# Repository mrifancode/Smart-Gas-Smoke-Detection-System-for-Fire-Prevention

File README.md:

## Didukung Oleh :
>- Dosen Pengampu : Akhmad Hendriawan ST., MT. (NIP.197501272002121003)
>- Mata kuliah : Mikrokontroller
>- Program Studi : D4 Teknik Elektronika
>- Politeknik Elektronika Negeri Surabaya<br>

## 🌊Board Member :

|      NRP      |       Nama      |    Jobdesk    |   Akun |
| :-----------:|:----------------:| :------------:| :-----:|
| 2122600031    | Annisa Nurfika Rani  | UI/UX       | [Annisaranii](https://github.com/Annisaranii)
| 2122600034    | Muhammad Rif'an        |  Project Manager | [mrifancode](https://github.com/mrifancode)
| 2122600035    | Admaeny Kusumas       |    UI/UX      | [admaeny](https://github.com/admaeny)
| 2122600044    | Kurniawan Putra Sugiharto  | Hardware | [Kurniawanputraa](https://github.com/Kurniawanputraa)
| 2122600058    | Muchammad Miftahus Shouni  | Program     | [Shoniiii](https://github.com/Shoniiii)

## 🧯 Smart Gas Smoke Detection System For Fire Prevention 👨‍🚒
Proyek ini merupakan sistem deteksi dini kebakaran berbasis mikrokontroler ATmega2560 (Arduino Mega) yang mampu mengenali keberadaan gas LPG dan asap di lingkungan sekitarnya. Sistem ini dirancang untuk memberikan peringatan secara otomatis melalui alarm buzzer dan indikator LED, serta menyediakan antarmuka GUI berbasis Python untuk pemantauan jarak dekat melalui komunikasi UART (serial).

Sensor gas dan asap seperti MQ-2 digunakan untuk mendeteksi senyawa mudah terbakar seperti LPG, asap hasil pembakaran, serta uap alkohol. Ketika konsentrasi gas atau asap melebihi ambang batas tertentu, sistem akan mengaktifkan alarm buzzer yang dikendalikan oleh sinyal PWM, sehingga mampu menghasilkan bunyi dengan intensitas berbeda tergantung level bahaya.

Selain alarm suara dan LED, sistem ini juga mengirimkan informasi status ke GUI yang menampilkan kondisi real-time, seperti konsentrasi gas, status sistem (aman atau bahaya), dan log waktu kejadian. Melalui GUI, pengguna juga dapat melakukan reset alarm, mengatur ambang batas, atau mengaktifkan simulasi kondisi bahaya untuk pengujian sistem.

## LOGO PRODUK ##

## 🔥🔥 Komponen Yang Digunakan 🔥🔥
 **1. 🤖Hardware**<br>
 
    a. Arduino ATmega 2560<br>
    b. Shield PCB<br>
    c. RTC<br>
    d. Sensor Gas MQ2<br>
    e. Sensor Asap MQ135<br>
    f. Camera <br>
    g. Buzzer <br>
    h. Indikator Lampu (led) <br>

**2. 💻Software**<br>

    a. KiCad<br>
    b. Inventor<br>
    c. Visual Studio Code (VSC)<br>
    d. Figma <br>

**3. 🪛Alat**<br>

    a. Solder<br>
    b. Timah solder<br>
    c. Kabel jumper<br>
    d. Breadboard<br>
    e. Obeng<br>
    f. PCB <br>
    g. Filamen <br>

## 🧰Rangkaian Simulasi 

## 🔮Alur Kerja

## 🚨Manfaat Project 🚨
Berikut adalah manfaat-manfaat yang didapatkan dari project kami:

1. **Pencegahan dini kebakaran** dengan mendeteksi gas/asap secara cepat, sistem dapat mencegah terjadinya kebakaran besar

2. **Meningkatkan keselamatan** penghuni rumah atau area yang dipantau.

3. **Mengurangi risiko** korban jiwa dan kerugian materi akibat kebakaran melalui sistem peringatan dini.

4. **Notifikasi real-time** memudahkan pengguna dan petugas keamanan dalam mengambil tindakan segera.

## 🔌🔌 HARDWARE 🔌🔌

**Berikut adalah jalur Wiring PCB yang kami buat menggunakan KICAD**

**Berikut adalah tampilan 3D PCB yang kami buat menggunakan KICAD**

## 🖼️🖼️ Desain 3D 🖼️🖼️ ##

**Berikut adalah 3D desain tampak luar**

**Berikut adalah 3D desain tampak dalam**

**Berikut adalah 3D desain tampak atas**

## 💻Tampilan GUI ##

## 📱Tampilan GUI WEB HP ##

## Video Promosi ##
https://youtu.be/rsLVeCHrQFU?si=O-Oxz26frcK8qSIt

## Link Canva ##
https://www.canva.com/design/DAGk-WylCwI/zFOLZ6zRMfbkMm96gKlujw/edit?utm_content=DAGk-WylCwI&utm_campaign=designshare&utm_medium=link2&utm_source=sharebutton

## Link Figma ##
https://www.figma.com/design/q9YQOLq4kY5U2ptUPi1XUb/web?fuid=1499084616784662598

## 💸💸 Rancangan Anggaran Biaya 💸💸

|      Nama Barang      |       Jumlah      |    Harga    |  
| :-----------:|:----------------:| :------------:| 
| Arduino ATmega2560    | 1  | Rp 180.000    | 
| MQ-135    |    1        |  Rp 23.500 | 
| MQ-2    |    1       |    Rp 14.300      | 
| Relay dual Channel    | 1  | Rp 20.250 | 
| PCB    | 1  | Rp 2.000     | 
| Kabel USB    | 1  | Rp5.000     | 
| Kabel Jumper    | 1pack  | Rp15.000     |   
| Kabel USB    | 1  | Rp5.000     |

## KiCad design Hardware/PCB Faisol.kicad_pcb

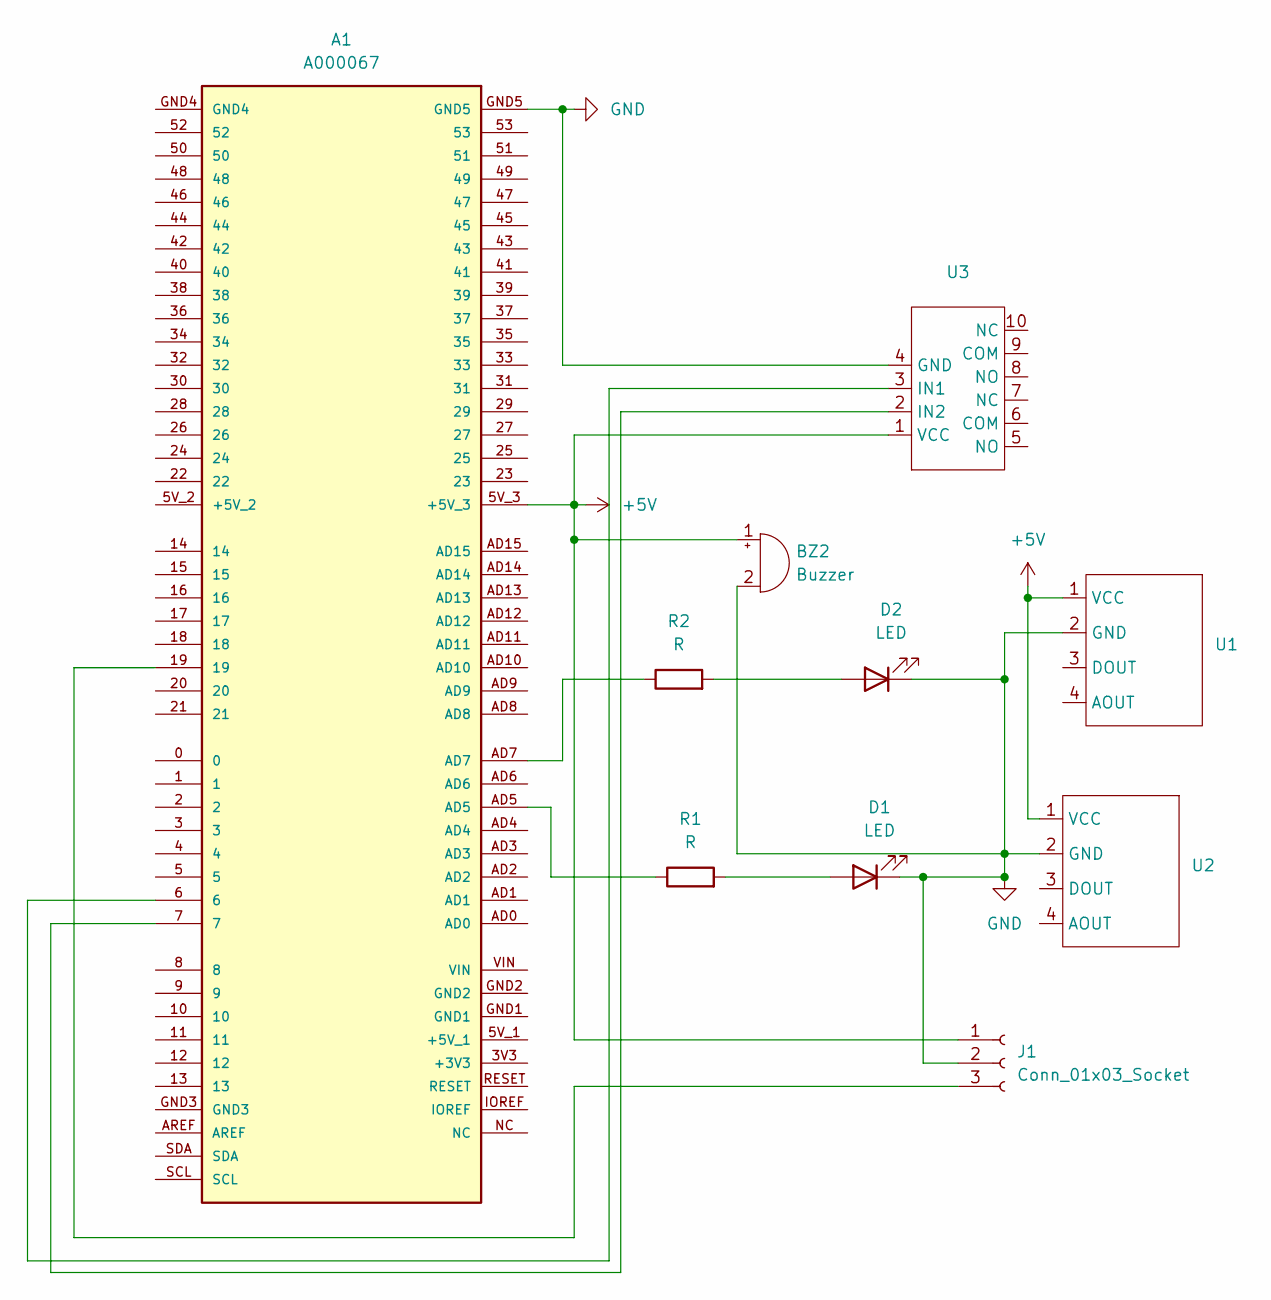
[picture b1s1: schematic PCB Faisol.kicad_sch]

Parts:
A1: A000067; MODULE_A000067; PARTREV 3
BZ2: Buzzer; Buzzer_12x9.5RM7.6
D1, D2: LED; LED_D1.8mm_W3.3mm_H2.4mm
J1: Conn_01x03_Socket; JST_XH_B3B-XH-A_1x03_P2.50mm_Vertical
R1, R2: R; R_Axial_DIN0204_L3.6mm_D1.6mm_P7.62mm_Horizontal
U1: MQ2
U2: MQ135
U3: dualRelay

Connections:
+5V: A1.5V_3 (+5V_3), BZ2.1 (+), J1.1, U1.1 (VCC), U2.1 (VCC), U3.1 (VCC)
GND: A1.GND5, BZ2.2 (-), D1.1 (K), D2.1 (K), J1.2, U1.2 (GND), U2.2 (GND), U3.4 (GND)
unnamed: A1.AD5, R1.1
unnamed: A1.AD7, R2.1
unnamed: D1.2 (A), R1.2
unnamed: D2.2 (A), R2.2
unnamed: A1.19, J1.3
unnamed: A1.6, U3.3 (IN1)
unnamed: A1.7, U3.2 (IN2)

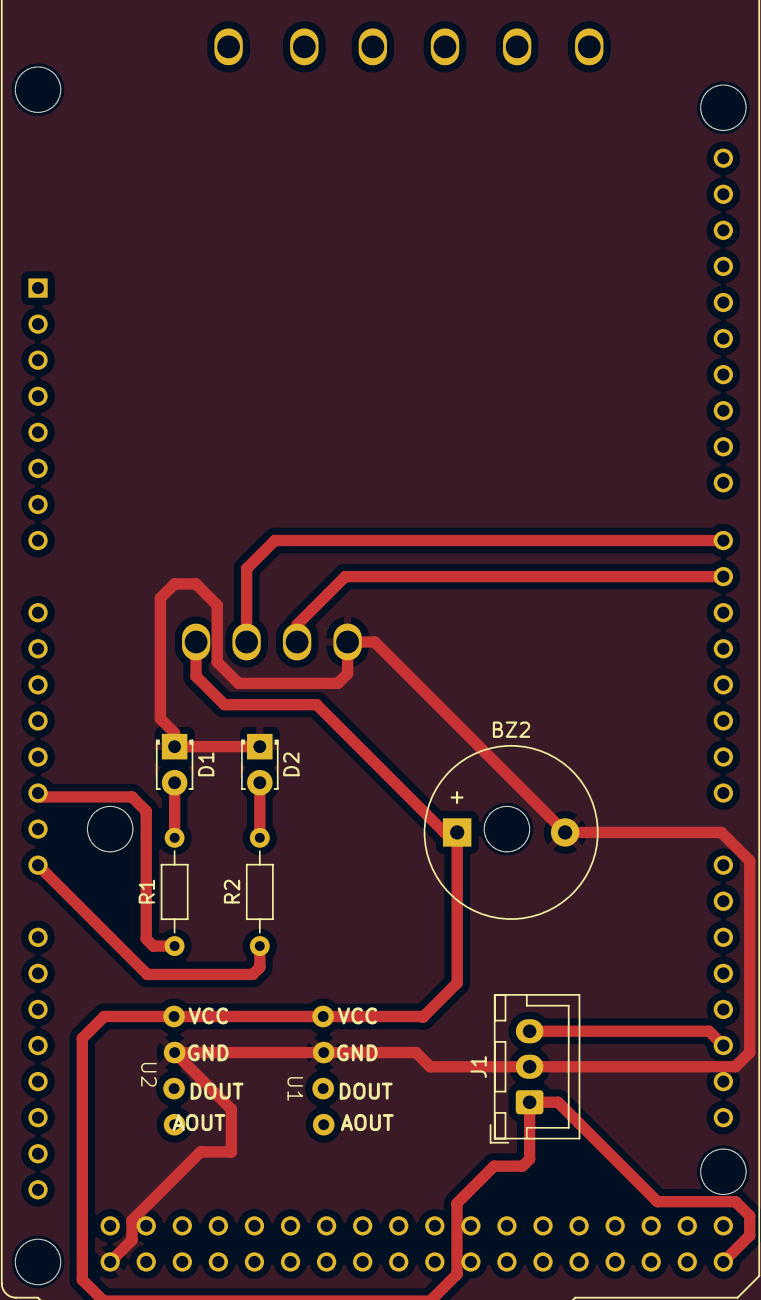
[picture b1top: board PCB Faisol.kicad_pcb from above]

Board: 2 copper layers, 10 parts (1 on the bottom side), 9 nets.

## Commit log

2025-05-11 GUI fix
    FIX bangett
2025-05-11 Create a
    buat file gui
2025-05-11 Create a
    buat file gui log history
2025-05-11 Create a
    buat file gui camera
2025-05-11 Add files via upload
    camera system fix
2025-05-11 tampilan file gambar
    tampilan gambar camera system
2025-05-11 file fix
    dashboard gui fix
2025-05-11 gui log history fix
    tampilan log history dan program fix
2025-06-02 Create test buzzer tanpa Lib
2025-06-02 Create tes led tanpa lib
2025-06-02 Create test mq135
2025-06-02 Create a
2025-06-03 Rename WhatsApp Image 2025-05-19 at 22.21.39_470adf7f.jpg to desain dashboard
2025-06-03 Rename Screenshot 2025-05-30 110030.png to desain
2025-06-03 Rename Screenshot 2025-05-30 110200.png to desain awal
2025-06-10 Rename desain web.png to DESAIN WEB.png
2025-06-10 Rename desain dashboard.jpg to desain dashboard hijau.jpg
2025-06-10 Rename desain kamera.png to desain kamera hijau.png
